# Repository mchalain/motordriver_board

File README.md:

Motordriver board
=================

This is a simple Kicad project for driver 3 stepper motors with a Raspberry Pico.

The project contains 2 boards:
 - "Carte Mere" where a Raspberry Pico must be plugged.
 - "Carte Driver" where the motor driver must be plugged.

1) The "Carte Mere":
It should be connected to a 24V DC alimentation, and produces 5V DC for the Raspberry Pico.

An I2C memory Flash may be added to store configuration of the Raspberry Pico.

3 jumpers help to define the "Carte Driver" connected to it.

2) The "Carte Driver":
It should be connected to the "Carte Mere" with two cables:
 - 5 wires for commands
 - 2 wires for 24V DC input

It carries a TMC2209 motor driver but it should accept other standard motor driver.

A endstop may be plugged to the board.

3) Usage:
The Raspberry Pico manages 3 stepper motors with the step/direction entries.

<details>
<summary>Stepper 1 connection:</summary>
 - 3.3 VDC
 - GND
 - Enab : GP 2
 - Step : GP 3
 - Dir  : GP 4
 - Orig : GP 5
</details>
<details>
<summary>Stepper 2 connection:</summary>
 - 3.3 VDC
 - GND
 - Enab : GP 6
 - Step : GP 7
 - Dir  : GP 8
 - Orig : GP 9
</details>
<details>
<summary>Stepper 3 connection:</summary>
 - 3.3 VDC
 - GND
 - Enab : GP 10
 - Step : GP 11
 - Dir  : GP 12
 - Orig : GP 13
</details>
<details>
<summary>Jumpers configuration:</summary>
 - JP1 : GP 18
 - JP2 : GP 19
 - JP3 : GP 20
</details>
<details>
<summary>I2C memory flash:</summary>
 - sda : GP0
 - scl : GP1
</details>

4) Software
The project may run with the project:

https://github.com/mchalain/stepperdriver

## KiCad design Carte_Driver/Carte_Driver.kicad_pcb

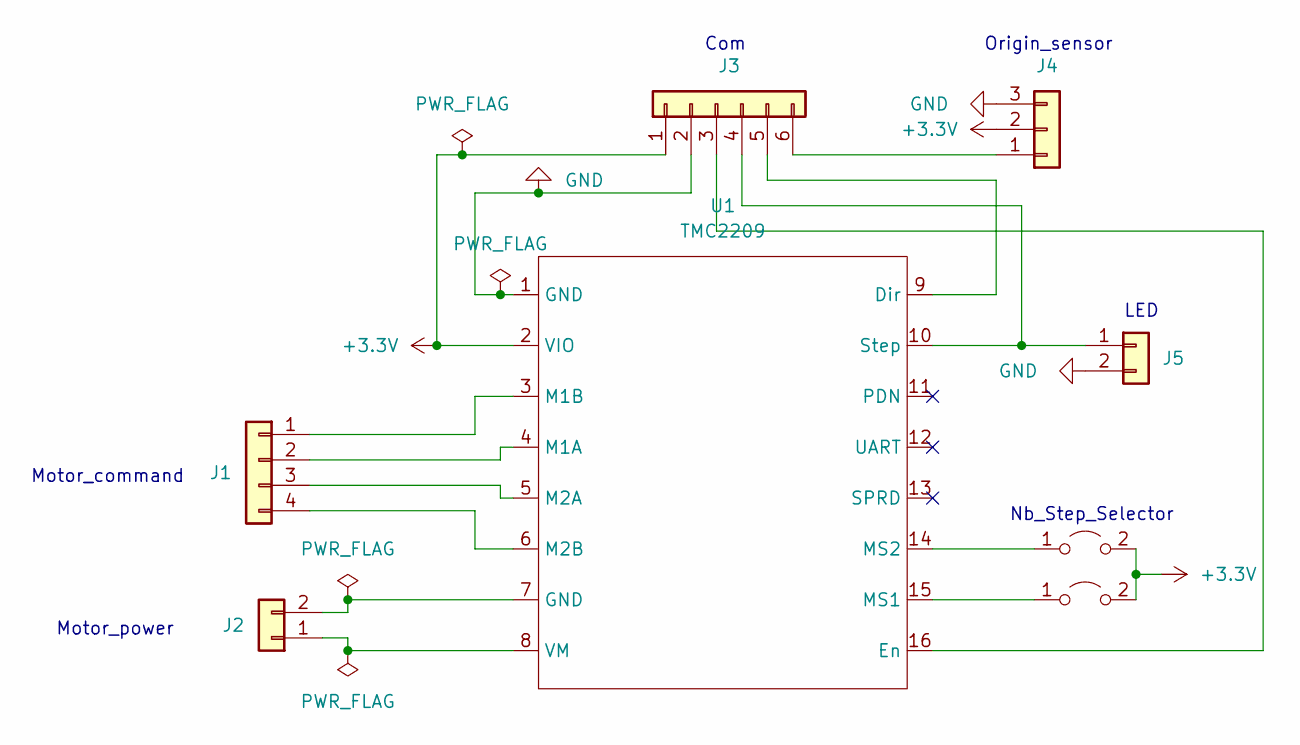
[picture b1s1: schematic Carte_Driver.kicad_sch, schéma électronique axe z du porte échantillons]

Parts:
J1: Conn_01x04; PinHeader_1x04_P2.54mm_Vertical
J2, J5: Conn_01x02; PinHeader_1x02_P2.54mm_Vertical
J3: Conn_01x06; PinHeader_1x06_P2.54mm_Vertical
J4: Conn_01x03; PinHeader_1x03_P2.54mm_Vertical
JP1, JP2: Jumper_2_Open; PinHeader_1x02_P2.54mm_Vertical
U1: TMC2209; Motor_driver_holder

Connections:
+3.3V: J3.1, J4.2, JP1.2 (B), JP2.2 (B), U1.2 (VIO)
GND: J3.2, J4.3, J5.2, U1.1 (GND)
unnamed: J1.1, U1.3 (M1B)
unnamed: J1.2, U1.4 (M1A)
unnamed: J1.3, U1.5 (M2A)
unnamed: J1.4, U1.6 (M2B)
unnamed: J2.1, U1.8 (VM)
unnamed: J2.2, U1.7 (GND)
unnamed: J3.3, U1.16 (En)
unnamed: J3.4, J5.1, U1.10 (Step)
unnamed: J3.5, U1.9 (Dir)
unnamed: J3.6, J4.1
unnamed: JP1.1 (A), U1.14 (MS2)
unnamed: JP2.1 (A), U1.15 (MS1)

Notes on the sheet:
Com
LED
Origin_sensor
Motor_power
Motor_command
Nb_Step_Selector

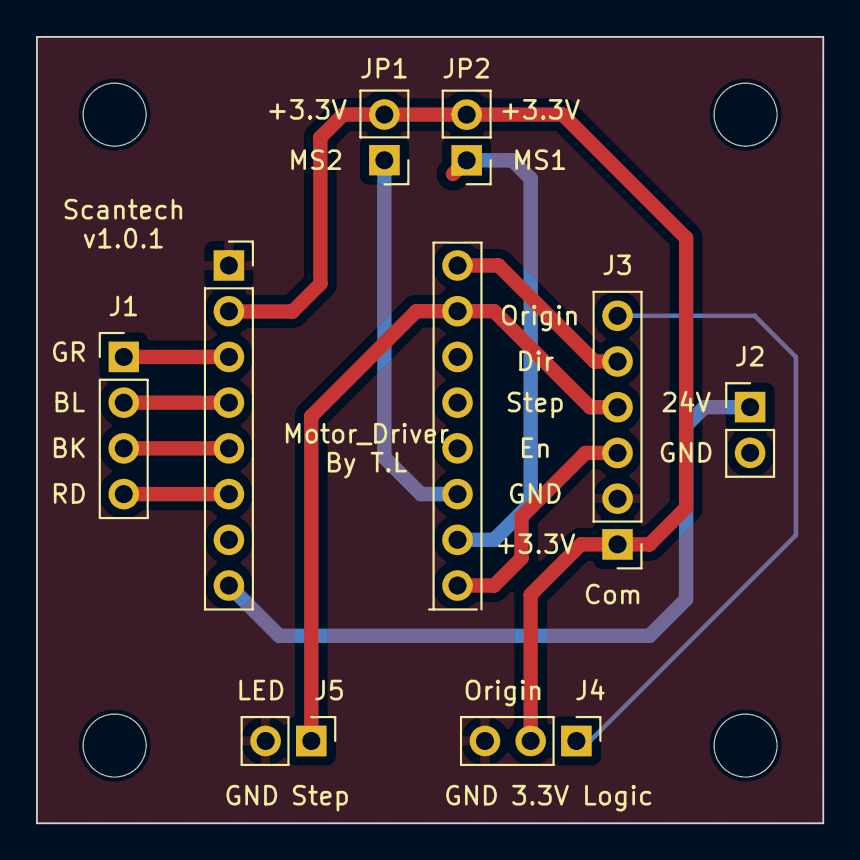
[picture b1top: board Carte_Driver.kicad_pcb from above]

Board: 2 copper layers, 43.7 x 43.7 mm, 8 parts (0 on the bottom side), 14 nets.

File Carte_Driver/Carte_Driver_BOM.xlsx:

Title | Driver_Holder_Card
Date: | lun. 17 juil. 2023 10:21:25
Version : | V1.0.0
 |  |  |  |  |  |  |  |  |  | Connecteur | HE13
Item | Quantity | Reference(s) | Value | Footprint | Datasheet | Manufacturer | REF_Manufacturer | Distributeur | REF_Distributeur | Distributeur | Ref Distributeur
1 | 1 | J1 | Conn_01x04 | Connector_PinHeader_2.54mm:PinHeader_1x04_P2.54mm_Vertical | ~ | TE Connectivity | 281696-4 | Mouser | 571-281696-4 | Farnell | 2112418
2 | 2 | J2, J5 | Conn_01x02 | Connector_PinHeader_2.54mm:PinHeader_1x02_P2.54mm_Vertical | ~ | TE Connectivity | 281696-2 | Mouser | 571-281696-2 | Farnell | 2112417
3 | 1 | J3 | Conn_01x06 | Connector_PinSocket_2.54mm:PinSocket_1x06_P2.54mm_Vertical | ~ | TE Connectivity | 281696-6 | Mouser | 571-281696-6 | Farnell | 2135956
4 | 1 | J4 | Conn_01x03 | Connector_PinHeader_2.54mm:PinHeader_1x03_P2.54mm_Vertical | ~ | TE Connectivity | 281696-3 | Mouser | 571-281696-3 | Farnell | 2490658
5 | 2 | JP1, JP2 | Jumper_2_Open | Connector_PinHeader_2.54mm:PinHeader_1x02_P2.54mm_Vertical | ~ | MOLEX | 22-28-4164 | Farnell | 3049546
6 | 1 | U1 | TMC2209 | LibraryFootprint:DriverFootprint |  | TRINAMIC / ANALOG DEVICES | TMC2209 SILENTSTEPSTICK | Farnell | 3131532 | Mouser | 855-M20-7822046

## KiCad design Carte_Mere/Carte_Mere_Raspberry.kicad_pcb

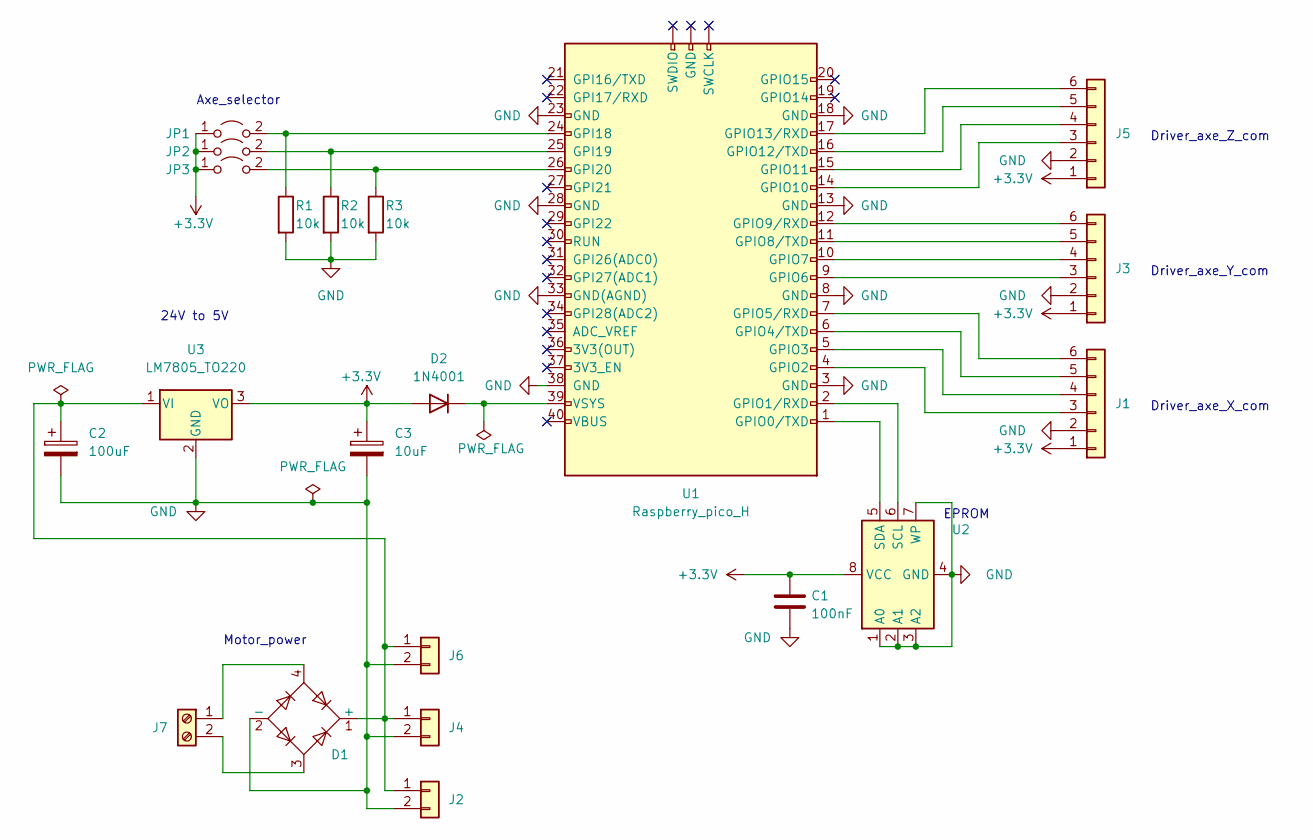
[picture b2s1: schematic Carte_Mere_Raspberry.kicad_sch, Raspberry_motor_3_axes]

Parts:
C1: 100nF; C_Rect_L7.0mm_W2.0mm_P5.00mm
C2: 100uF; C_Rect_L7.0mm_W2.0mm_P5.00mm
C3: 10uF; C_Rect_L7.0mm_W2.0mm_P5.00mm
D1: ABS2; Diode_Bridge_Diotec_ABS
D2: 1N4001; D_DO-41_SOD81_P10.16mm_Horizontal
J1, J3, J5: Conn_01x06; PinHeader_1x06_P2.54mm_Vertical
J2, J4, J6: Conn_01x02; PinHeader_1x02_P2.54mm_Vertical
J7: Screw_Terminal_01x02; TerminalBlock_bornier-2_P5.08mm
JP1, JP2, JP3: Jumper_2_Open; PinHeader_1x02_P2.54mm_Vertical
R1, R2, R3: 10k; R_Axial_DIN0207_L6.3mm_D2.5mm_P7.62mm_Horizontal
U1: Raspberry_pico_H; foo
U2: 24LC01; DIP-8_W7.62mm
U3: LM7805_TO220; TO-220-3_Vertical

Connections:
+3.3V: C1.1, C3.1, D2.2 (A), J1.1, J3.1, J5.1, JP1.1 (A), JP2.1 (A), JP3.1 (A), U2.8 (VCC), U3.3 (VO)
GND: C1.2, C2.2, C3.2, D1.2 (-), J1.2, J2.2, J3.2, J4.2, J5.2, J6.2, R1.2, R2.2, R3.2, U1.3 (GND), U1.8 (GND), U1.13 (GND), U1.18 (GND), U1.23 (GND), U1.28 (GND), U1.33 (GND(AGND)), U1.38 (GND), U2.1 (A0), U2.2 (A1), U2.3 (A2), U2.4 (GND), U2.7 (WP), U3.2 (GND)
unnamed: C2.1, D1.1 (+), J2.1, J4.1, J6.1, U3.1 (VI)
unnamed: D1.3, J7.2
unnamed: D1.4, J7.1
unnamed: D2.1 (K), U1.39 (VSYS)
unnamed: J1.3, U1.4 (GPIO2)
unnamed: J1.4, U1.5 (GPIO3)
unnamed: J1.5, U1.6 (GPIO4/TXD)
unnamed: J1.6, U1.7 (GPIO5/RXD)
unnamed: J3.3, U1.9 (GPIO6)
unnamed: J3.4, U1.10 (GPIO7)
unnamed: J3.5, U1.11 (GPIO8/TXD)
unnamed: J3.6, U1.12 (GPIO9/RXD)
unnamed: J5.3, U1.14 (GPIO10)
unnamed: J5.4, U1.15 (GPIO11)
unnamed: J5.5, U1.16 (GPIO12/TXD)
unnamed: J5.6, U1.17 (GPIO13/RXD)
unnamed: JP1.2 (B), R1.1, U1.24 (GPI18)
unnamed: JP2.2 (B), R2.1, U1.25 (GPI19)
unnamed: JP3.2 (B), R3.1, U1.26 (GPI20)
unnamed: U1.1 (GPIO0/TXD), U2.5 (SDA)
unnamed: U1.2 (GPIO1/RXD), U2.6 (SCL)

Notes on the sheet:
Driver_axe_Y_com
Driver_axe_Z_com
Driver_axe_X_com
Motor_power
24V to 5V
EPROM
Axe_selector

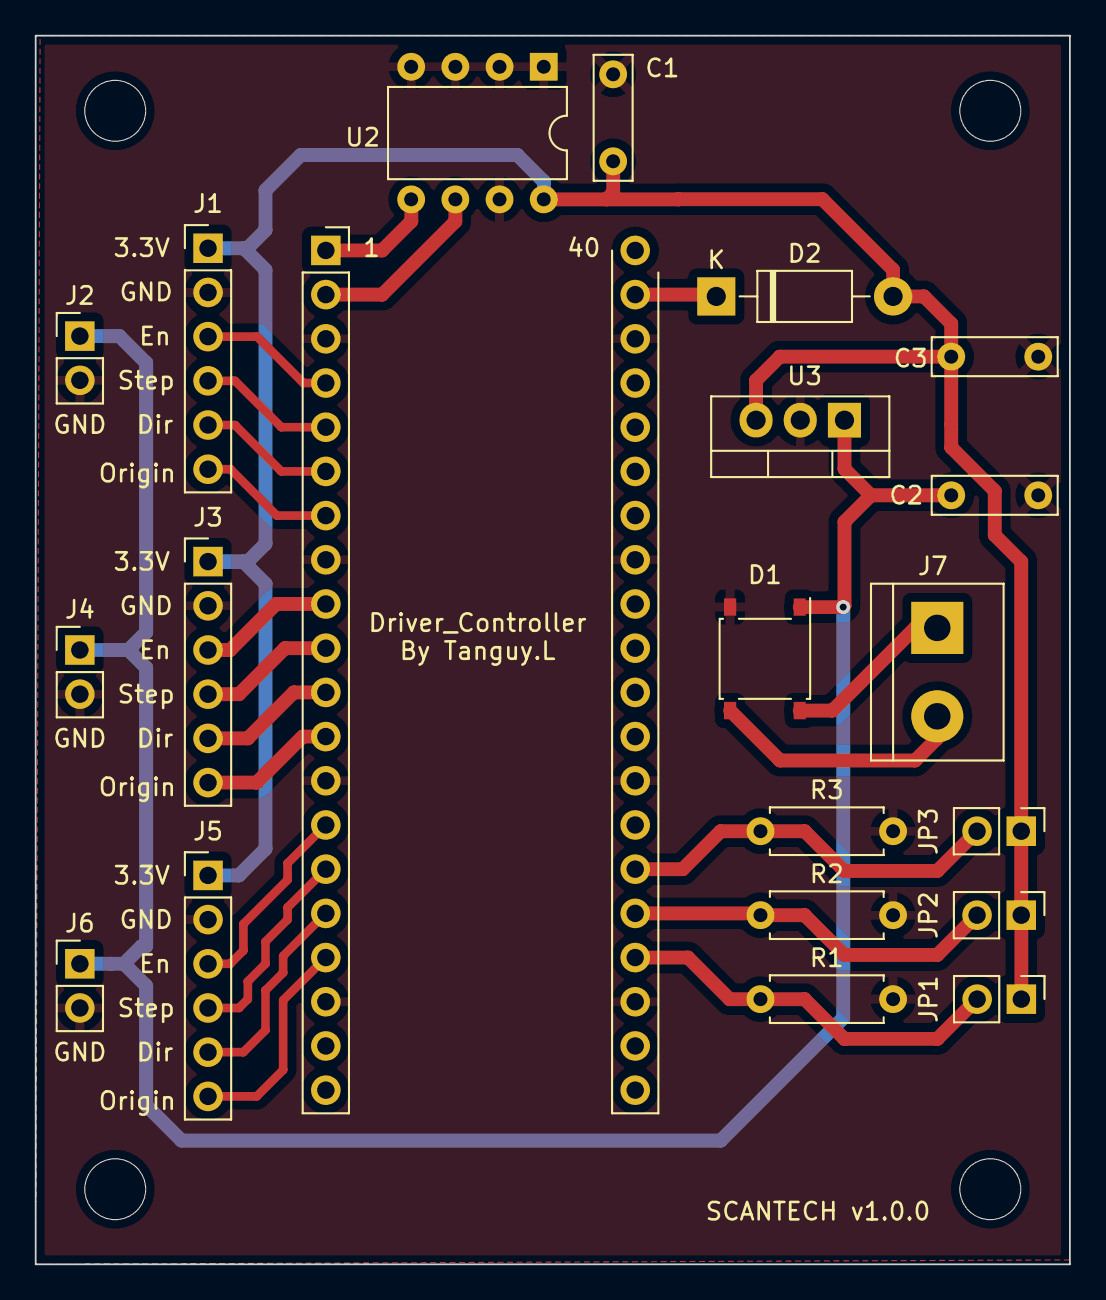
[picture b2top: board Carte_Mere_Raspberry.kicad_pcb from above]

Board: 2 copper layers, 59.4 x 70.6 mm, 21 parts (0 on the bottom side), 23 nets.

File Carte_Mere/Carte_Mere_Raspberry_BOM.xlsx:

Titre | Driver_Controller
Date | 45134
 |  |  |  |  |  |  |  |  |  | Connecteur | HE13
Id | Référence | Empreinte | Quantité | Désignation | Datasheet | Fabricant | Ref Fabricant | Distributeur | Ref Distributeur | Distributeur | Ref Distributeur
1 | R3,R1,R2 | R_Axial_DIN0207_L6.3mm_D2.5mm_P7.62mm_Horizontal | 3 | 10k
2 | C1 | C_Rect_L7.0mm_W2.0mm_P5.00mm | 1 | 100nF
3 | C3 | C_Rect_L7.0mm_W2.0mm_P5.00mm | 1 | 10uF
4 | C2 | C_Rect_L7.0mm_W2.0mm_P5.00mm | 1 | 100uF
5 | J3,J5,J1 | PinHeader_1x06_P2.54mm_Vertical | 3 | Conn_01x06 |  | TE Connectivity | 281696-6 | Mouser | 571-281696-6 | Farnell | 2135956
6 | JP3,JP1,JP2 | PinHeader_1x02_P2.54mm_Vertical | 3 | Jumper_2_Open |  | MOLEX | 22-28-4164 | Farnell | 3049546
7 | J6,J4,J2 | PinHeader_1x02_P2.54mm_Vertical | 3 | Conn_01x02 |  | TE Connectivity | 281696-2 | Mouser | 571-281696-2 | Farnell | 2112417
8 | U3 | TO-220-3_Vertical | 1 | LM7805_TO220 | C:\Users\Install\Desktop\Cartes_electronique_marc\Cartes_electronique_marc\Data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 | STMicroelectronics | L7805CV | Mouser | 511-L7805CV
9 | U2 | DIP-8_W7.62mm | 1 | 24LC01 | C:\Users\Install\Desktop\Cartes_electronique_marc\Cartes_electronique_marc\Data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 | MICROCHIP | 24LC01B/P | Farnell | 1200025
10 | D2 | D_DO-41_SOD81_P10.16mm_Horizontal | 1 | 1N4001 |  | AMERICAN POWER DEVICES | 1N4001 | Farnell | 1651089
11 | D1 | Diode_Bridge_Diotec_ABS | 1 | ABS2 |  | MULTICOMP PRO | ABS2 | Farnell | 1857467
12 | J7 | TerminalBlock_bornier-2_P5.08mm | 1 | Screw_Terminal_01x02 |  | BUCHANAN - TE CONNECTIVITY | 282837-2 | Farnell | 1784860
13 | U1 | foo | 1 | Raspberry_pico_H | C:\Users\Install\Desktop\Cartes_electronique_marc\Cartes_electronique_marc\Data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 | RASPBERRY-PI | RASPBERRY PI PICO H | Farnell | 3996081 | Mouser | 855-M20-7822046

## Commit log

2023-10-23 first release from Tanguy Lambert
2023-10-23 Documentation
